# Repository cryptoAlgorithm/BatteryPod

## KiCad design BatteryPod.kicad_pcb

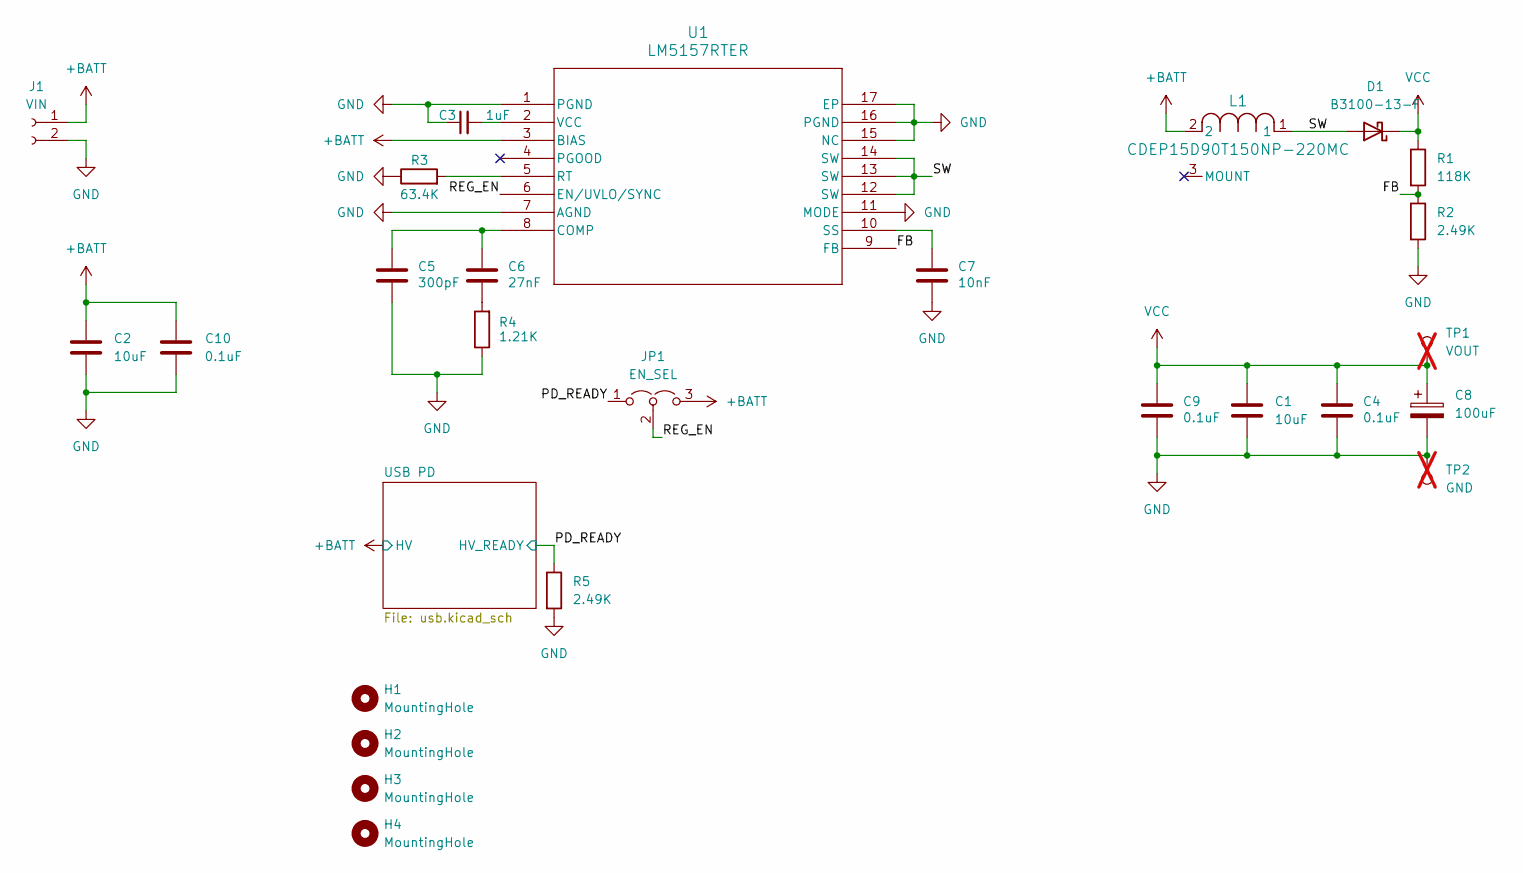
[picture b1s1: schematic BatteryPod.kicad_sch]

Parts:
C1, C2: 10uF; C_2220_5750Metric; Part C342280
C3: 1uF; C_0603_1608Metric; Part C342988
C4, C9, C10: 0.1uF; C_0603_1608Metric; Part C597287
C5: 300pF; C_0603_1608Metric; Part C159791
C6: 27nF; C_0603_1608Metric; Part C107086
C7: 10nF; C_0603_1608Metric; Part C307347
C8: 100uF; CP_Elec_10x10; Part C487156
D1: B3100-13-F; D_SMC; Part C134447
H1, H2, H3, H4: MountingHole; MountingHole_2.5mm
J1: VIN; SolderWire-1.5sqmm_1x02_P7.8mm_D1.7mm_OD3.9mm
JP1: EN_SEL; PinHeader_1x03_P2.54mm_Vertical
L1: CDEP15D90T150NP-220MC; Part C171581
R1: 118K; R_0603_1608Metric; Part C234251
R2, R5: 2.49K; R_0603_1608Metric; Part C491121
R3: 63.4K; R_0603_1608Metric; Part C218107
R4: 1.21K; R_0603_1608Metric; Part C705737
TP1: VOUT; TestPoint_Loop_D2.50mm_Drill1.0mm_LowProfile; not fitted
TP2: GND; TestPoint_Loop_D2.50mm_Drill1.0mm_LowProfile; not fitted
U1: LM5157RTER; QFN_57RTER_TEX; Part C3188436

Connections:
+BATT: C2.1, C10.2, J1.1, JP1.3 (B), L1.2, U1.3 (BIAS); also elsewhere on the board
/FB: R1.2, R2.1, U1.9 (FB)
/PD_READY: JP1.1 (A), R5.1; also elsewhere on the board
/REG_EN: JP1.2 (C), U1.6 (EN/UVLO/SYNC)
/SW: D1.2 (A), L1.1, U1.12 (SW), U1.13 (SW), U1.14 (SW)
GND: C1.2, C2.2, C3.1, C4.2, C5.2, C7.2, C8.2, C9.2, C10.1, J1.2, R2.2, R3.1, R4.1, R5.2, TP2.1, U1.1 (PGND), U1.7 (AGND), U1.11 (MODE), U1.15 (NC), U1.16 (PGND), U1.17 (EP); also elsewhere on the board
unnamed: C6.2, R4.2
unnamed: C5.1, C6.1, U1.8 (COMP)
unnamed: R3.2, U1.5 (RT)
unnamed: C7.1, U1.10 (SS)
unnamed: C3.2, U1.2 (VCC)
VCC: C1.1, C4.1, C8.1, C9.1, D1.1 (K), R1.1, TP1.1

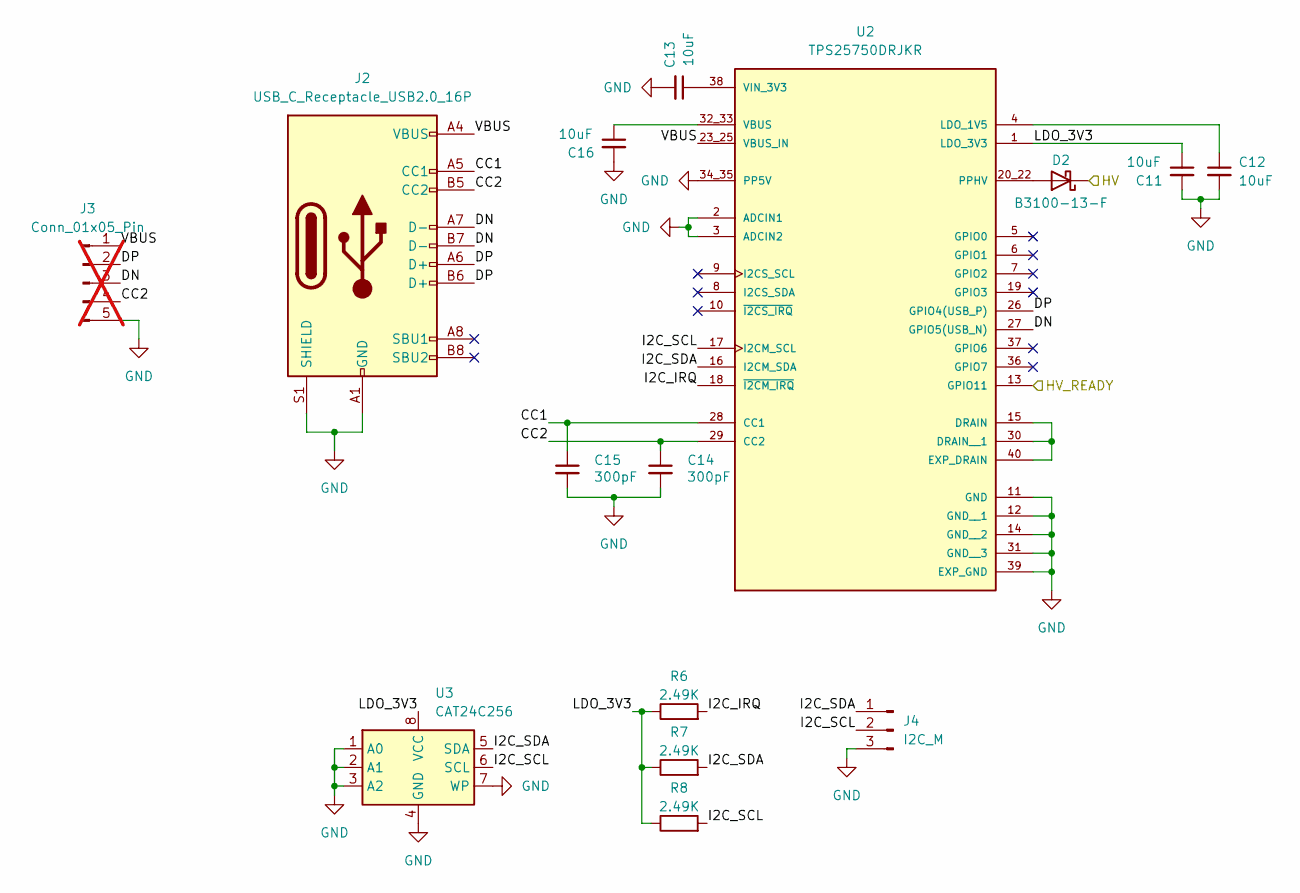
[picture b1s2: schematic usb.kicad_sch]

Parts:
C11, C12, C13, C16: 10uF; C_0402_1005Metric; Part C2992625
C14, C15: 300pF; C_0603_1608Metric; Part C159791
D2: B3100-13-F; D_SMC; Part C134447
J2: USB_C_Receptacle_USB2.0_16P; USB_C_Receptacle_G-Switch_GT-USB-7010ASV; Part C2843968
J3: Conn_01x05_Pin; PinHeader_1x05_P2.54mm_Vertical; not fitted
J4: I2C_M; PinHeader_1x03_P2.54mm_Vertical
R6, R7, R8: 2.49K; R_0603_1608Metric; Part C491121
U2: TPS25750DRJKR; IC_TPS25750DRJKR; PARTREV A
U3: CAT24C256; SOIC-8_3.9x4.9mm_P1.27mm; Part C79987

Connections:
+BATT: D2.1 (K); also elsewhere on the board
/PD_READY: U2.13 (GPIO11); also elsewhere on the board
/USB PD/CC1: C15.1, J2.A5 (CC1), U2.28 (CC1)
/USB PD/CC2: C14.1, J2.B5 (CC2), J3.4, U2.29 (CC2)
/USB PD/DN: J2.A7 (D-), J2.B7 (D-), J3.3, U2.27 (GPIO5(USB_N))
/USB PD/DP: J2.A6 (D+), J2.B6 (D+), J3.2, U2.26 (GPIO4(USB_P))
/USB PD/I2C_IRQ: R6.2, U2.18 (~I2CM_IRQ)
/USB PD/I2C_SCL: J4.2, R8.2, U2.17 (I2CM_SCL), U3.6 (SCL)
/USB PD/I2C_SDA: J4.1, R7.2, U2.16 (I2CM_SDA), U3.5 (SDA)
/USB PD/LDO_3V3: C11.1, R6.1, R7.1, R8.1, U2.1 (LDO_3V3), U3.8 (VCC)
/USB PD/VBUS: J2.A4 (VBUS), J2.A9 (VBUS), J2.B4 (VBUS), J2.B9 (VBUS), J3.1, U2.23_25 (VBUS_IN)
GND: C11.2, C12.2, C13.2, C14.2, C15.2, C16.2, J2.A1 (GND), J2.A12 (GND), J2.B1 (GND), J2.B12 (GND), J2.S1 (SHIELD), J3.5, J4.3, U2.2 (ADCIN1), U2.3 (ADCIN2), U2.11 (GND), U2.12 (GND__1), U2.14 (GND__2), U2.31 (GND__3), U2.34_35 (PP5V), U2.39 (EXP_GND), U3.1 (A0), U3.2 (A1), U3.3 (A2), U3.4 (GND), U3.7 (WP); also elsewhere on the board
unnamed: D2.2 (A), U2.20_22 (PPHV)
unnamed: U2.15 (DRAIN), U2.30 (DRAIN__1), U2.40 (EXP_DRAIN)
unnamed: C12.1, U2.4 (LDO_1V5)
unnamed: C16.1, U2.32_33 (VBUS)
unnamed: C13.1, U2.38 (VIN_3V3)

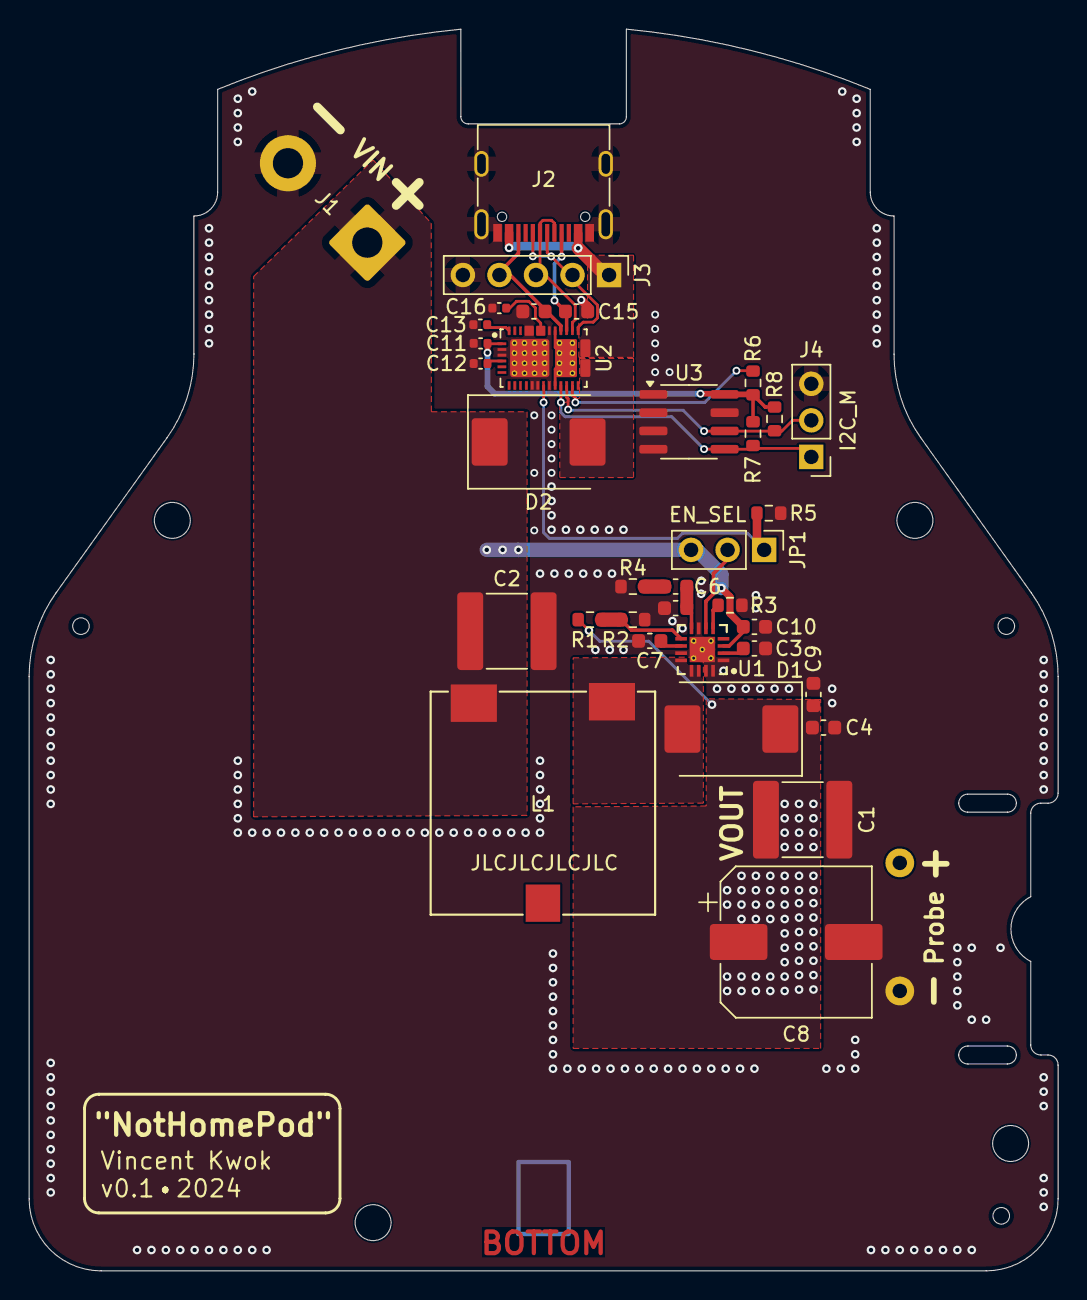
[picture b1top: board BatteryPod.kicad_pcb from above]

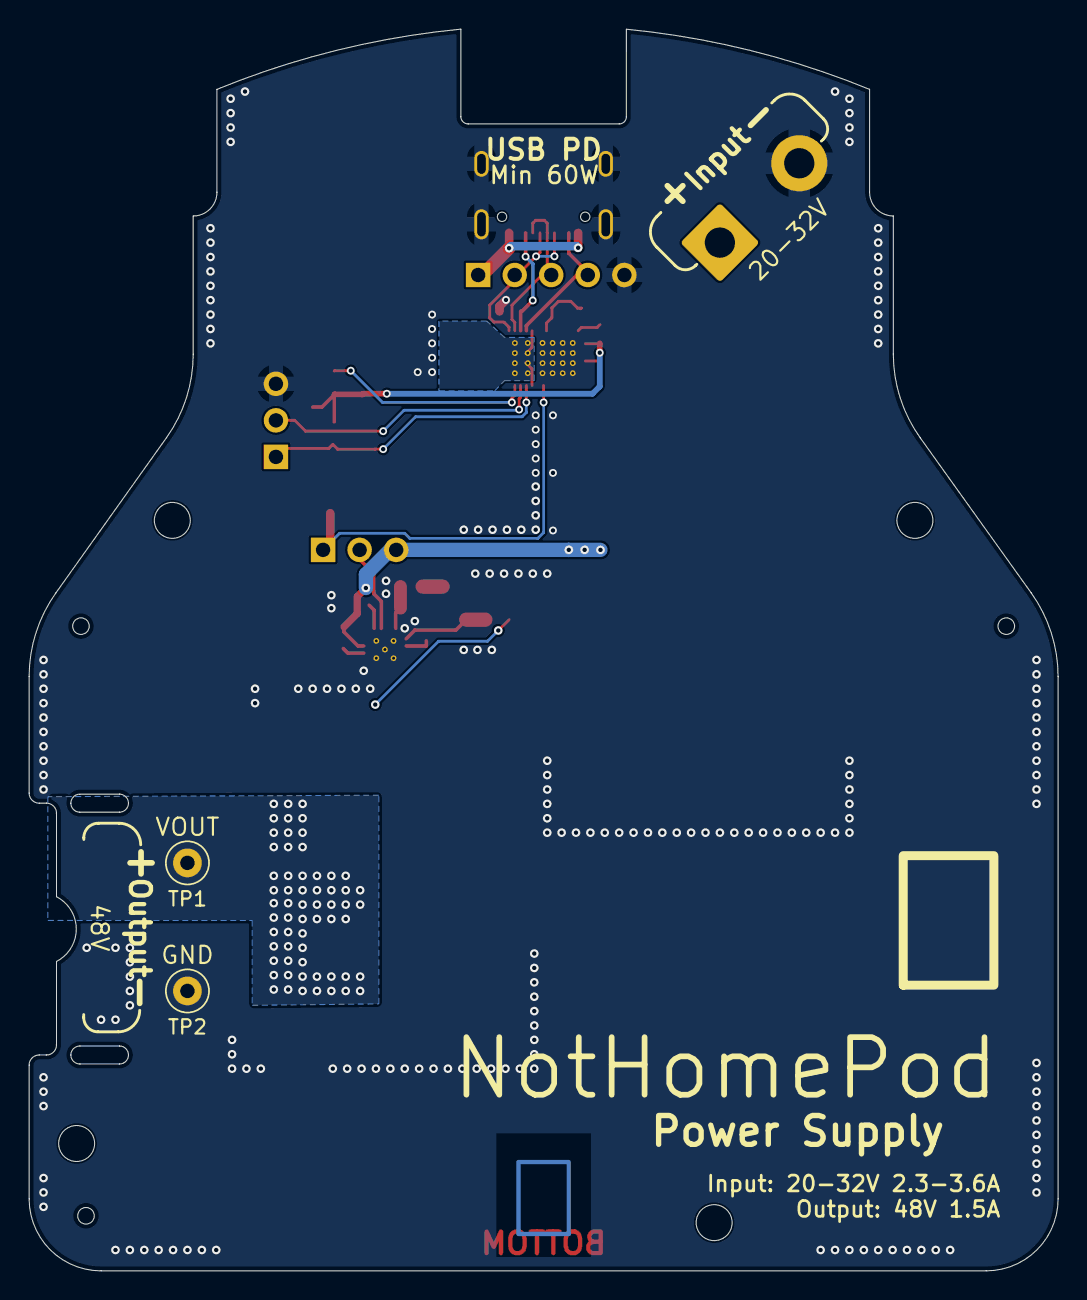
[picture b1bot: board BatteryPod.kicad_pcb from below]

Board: 2 copper layers, 71.5 x 86.3 mm, 41 parts (6 on the bottom side), 26 nets.

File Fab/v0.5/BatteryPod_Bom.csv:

"Designator","Comment","Footprint","JLCPCB Part #"
"U1","LM5157RTER","lm5157:QFN_57RTER_TEX","C3188436"
"C11,C12,C13,C16","10uF","Capacitor_SMD:C_0402_1005Metric","C2992625"
"U2","TPS25750DRJKR","Ti:IC_TPS25750DRJKR","C2868209"
"J2","USB_C_Receptacle_USB2.0_16P","Connector_USB:USB_C_Receptacle_G-Switch_GT-USB-7010ASV","C2843968"
"R4","1.21K","Resistor_SMD:R_0603_1608Metric","C705737"
"C4,C9,C10","0.1uF","Capacitor_SMD:C_0603_1608Metric","C597287"
"R2,R5,R6,R7,R8","2.49K","Resistor_SMD:R_0603_1608Metric","C491121"
"C8","100uF","Capacitor_SMD:CP_Elec_10x10","C487156"
"C3","1uF","Capacitor_SMD:C_0603_1608Metric","C342988"
"C1,C2","10uF","Capacitor_SMD:C_2220_5750Metric","C342280"
"C7","10nF","Capacitor_SMD:C_0603_1608Metric","C307347"
"R1","118K","Resistor_SMD:R_0603_1608Metric","C234251"
"R3","63.4K","Resistor_SMD:R_0603_1608Metric","C218107"
"L1","CDEP15D90T150NP-220MC","Sumida:CDEP15D90T150NP-220MC","C171581"
"C5,C14,C15","300pF","Capacitor_SMD:C_0603_1608Metric","C159791"
"D1,D2","B3100-13-F","Diode_SMD:D_SMC","C134447"
"C6","27nF","Capacitor_SMD:C_0603_1608Metric","C107086"
"U3","CAT24C256","Package_SO:SOIC-8_3.9x4.9mm_P1.27mm","C79987"

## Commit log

2024-04-30 feat: inital commit with circuit and board outline
2024-05-01 feat: almost full initial routing
2024-05-01 feat: correct screw positioning (hopefully)
2024-05-01 patch: silkscreen improvements fix: screw hole position
2024-05-01 feat: add output pads
2024-05-02 feat: move to lower half of board due to high profile inductor this is to match with a recess in the chassis for the higher profile component
2024-05-02 fix: drc errors
2024-05-06 feat: add partial USB-PD input, routing
2024-05-07 feat: fully routed USB-PD, new lower profile inductor
2024-05-26 patch: final trace cleaups/parameter updates
